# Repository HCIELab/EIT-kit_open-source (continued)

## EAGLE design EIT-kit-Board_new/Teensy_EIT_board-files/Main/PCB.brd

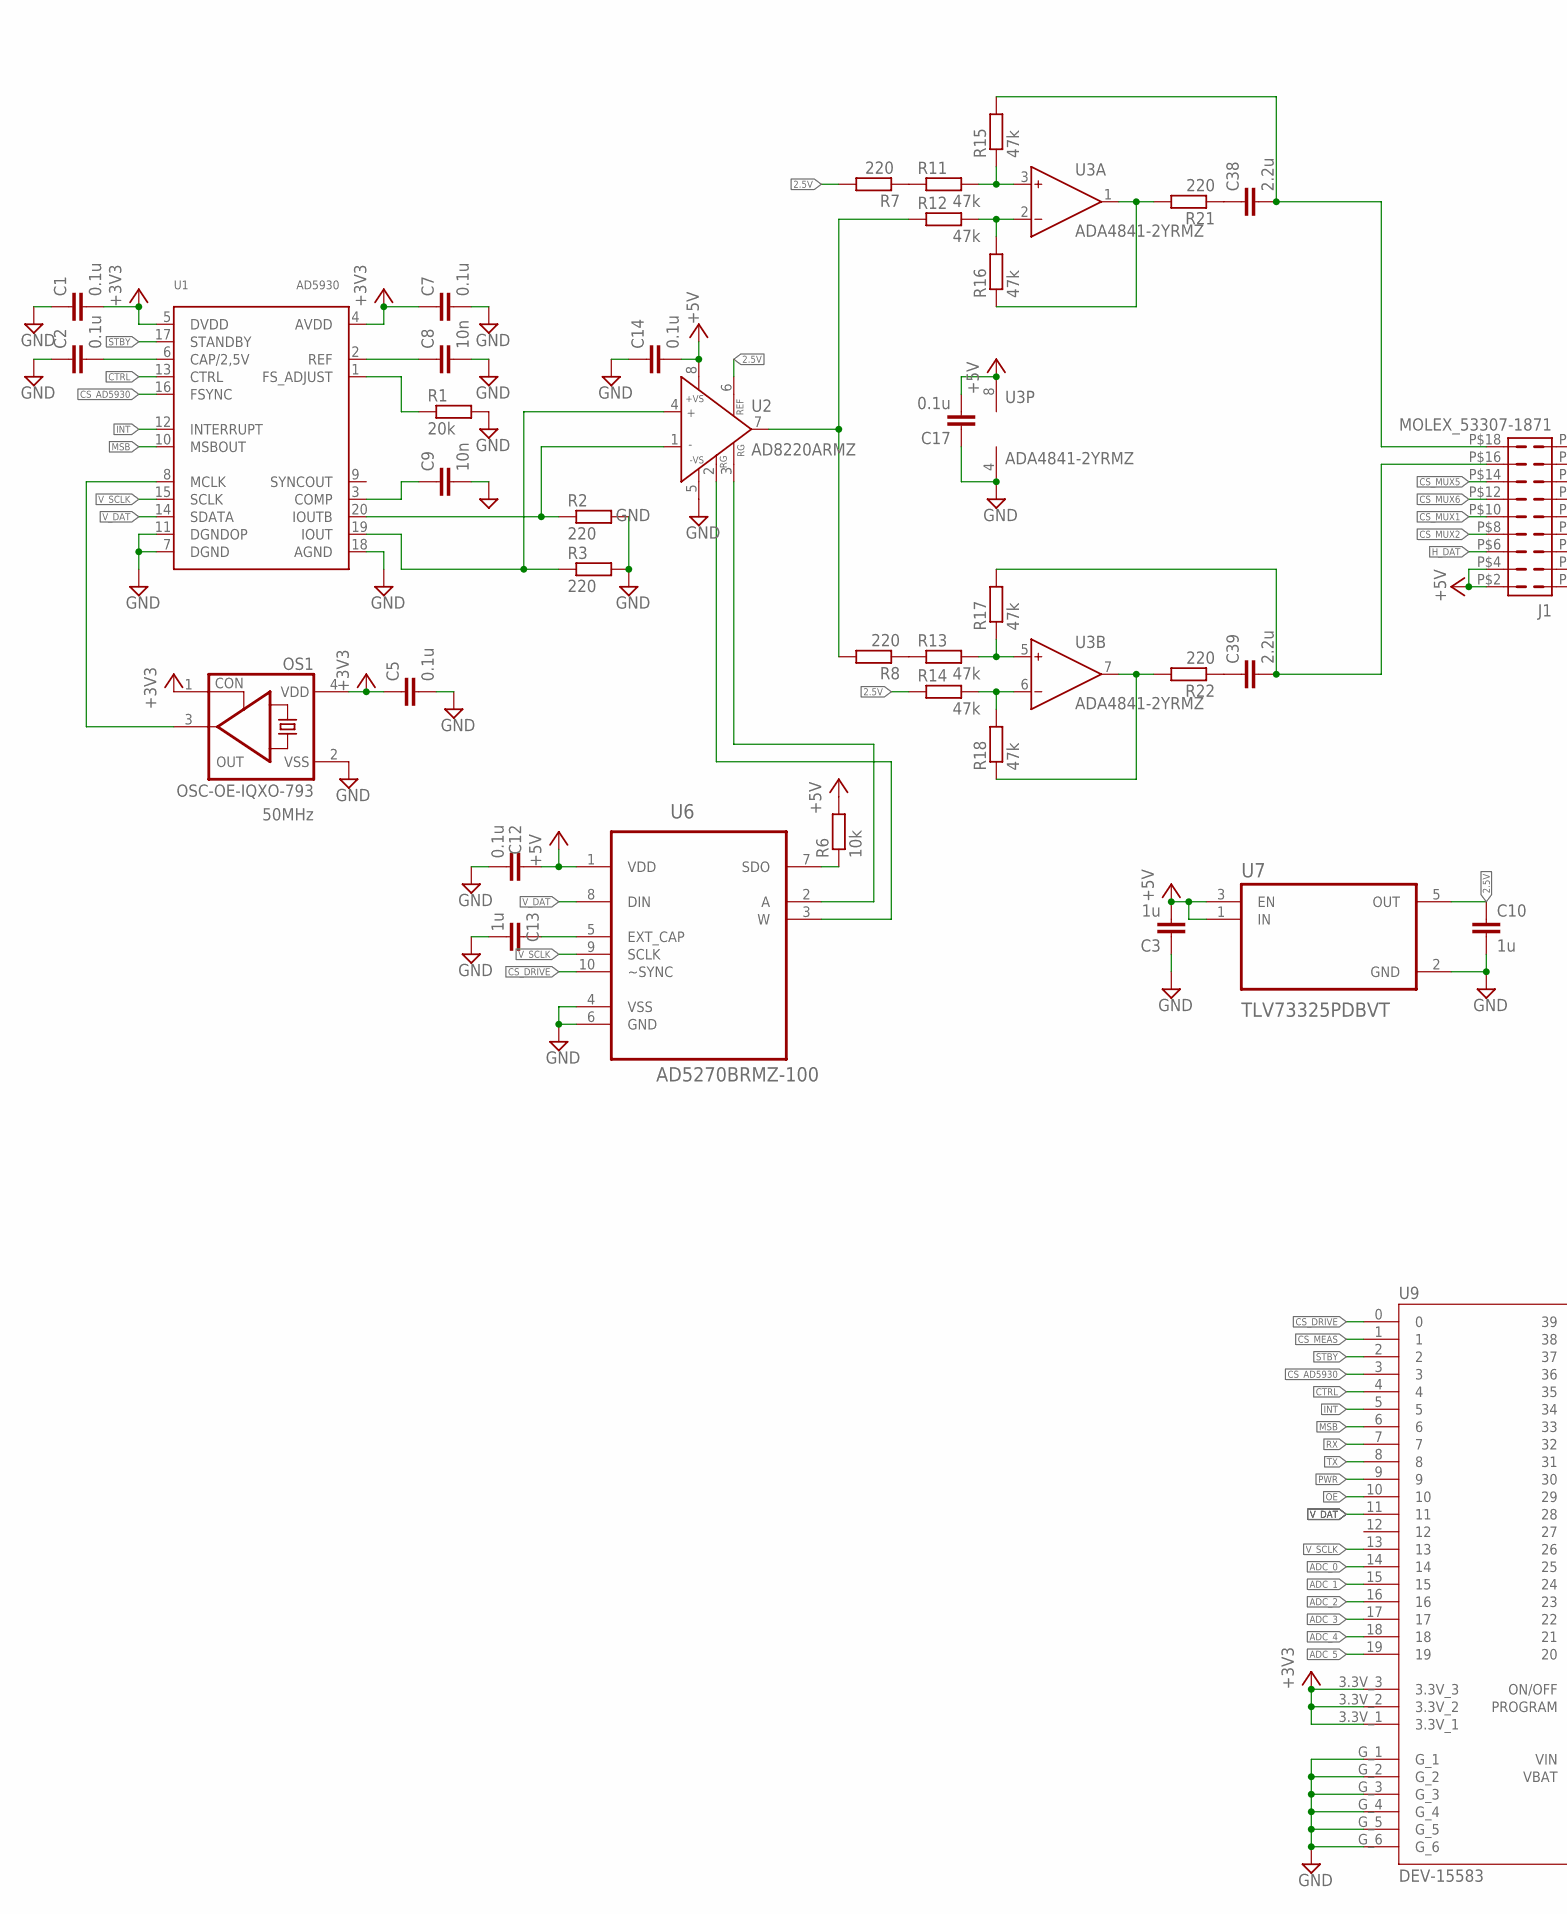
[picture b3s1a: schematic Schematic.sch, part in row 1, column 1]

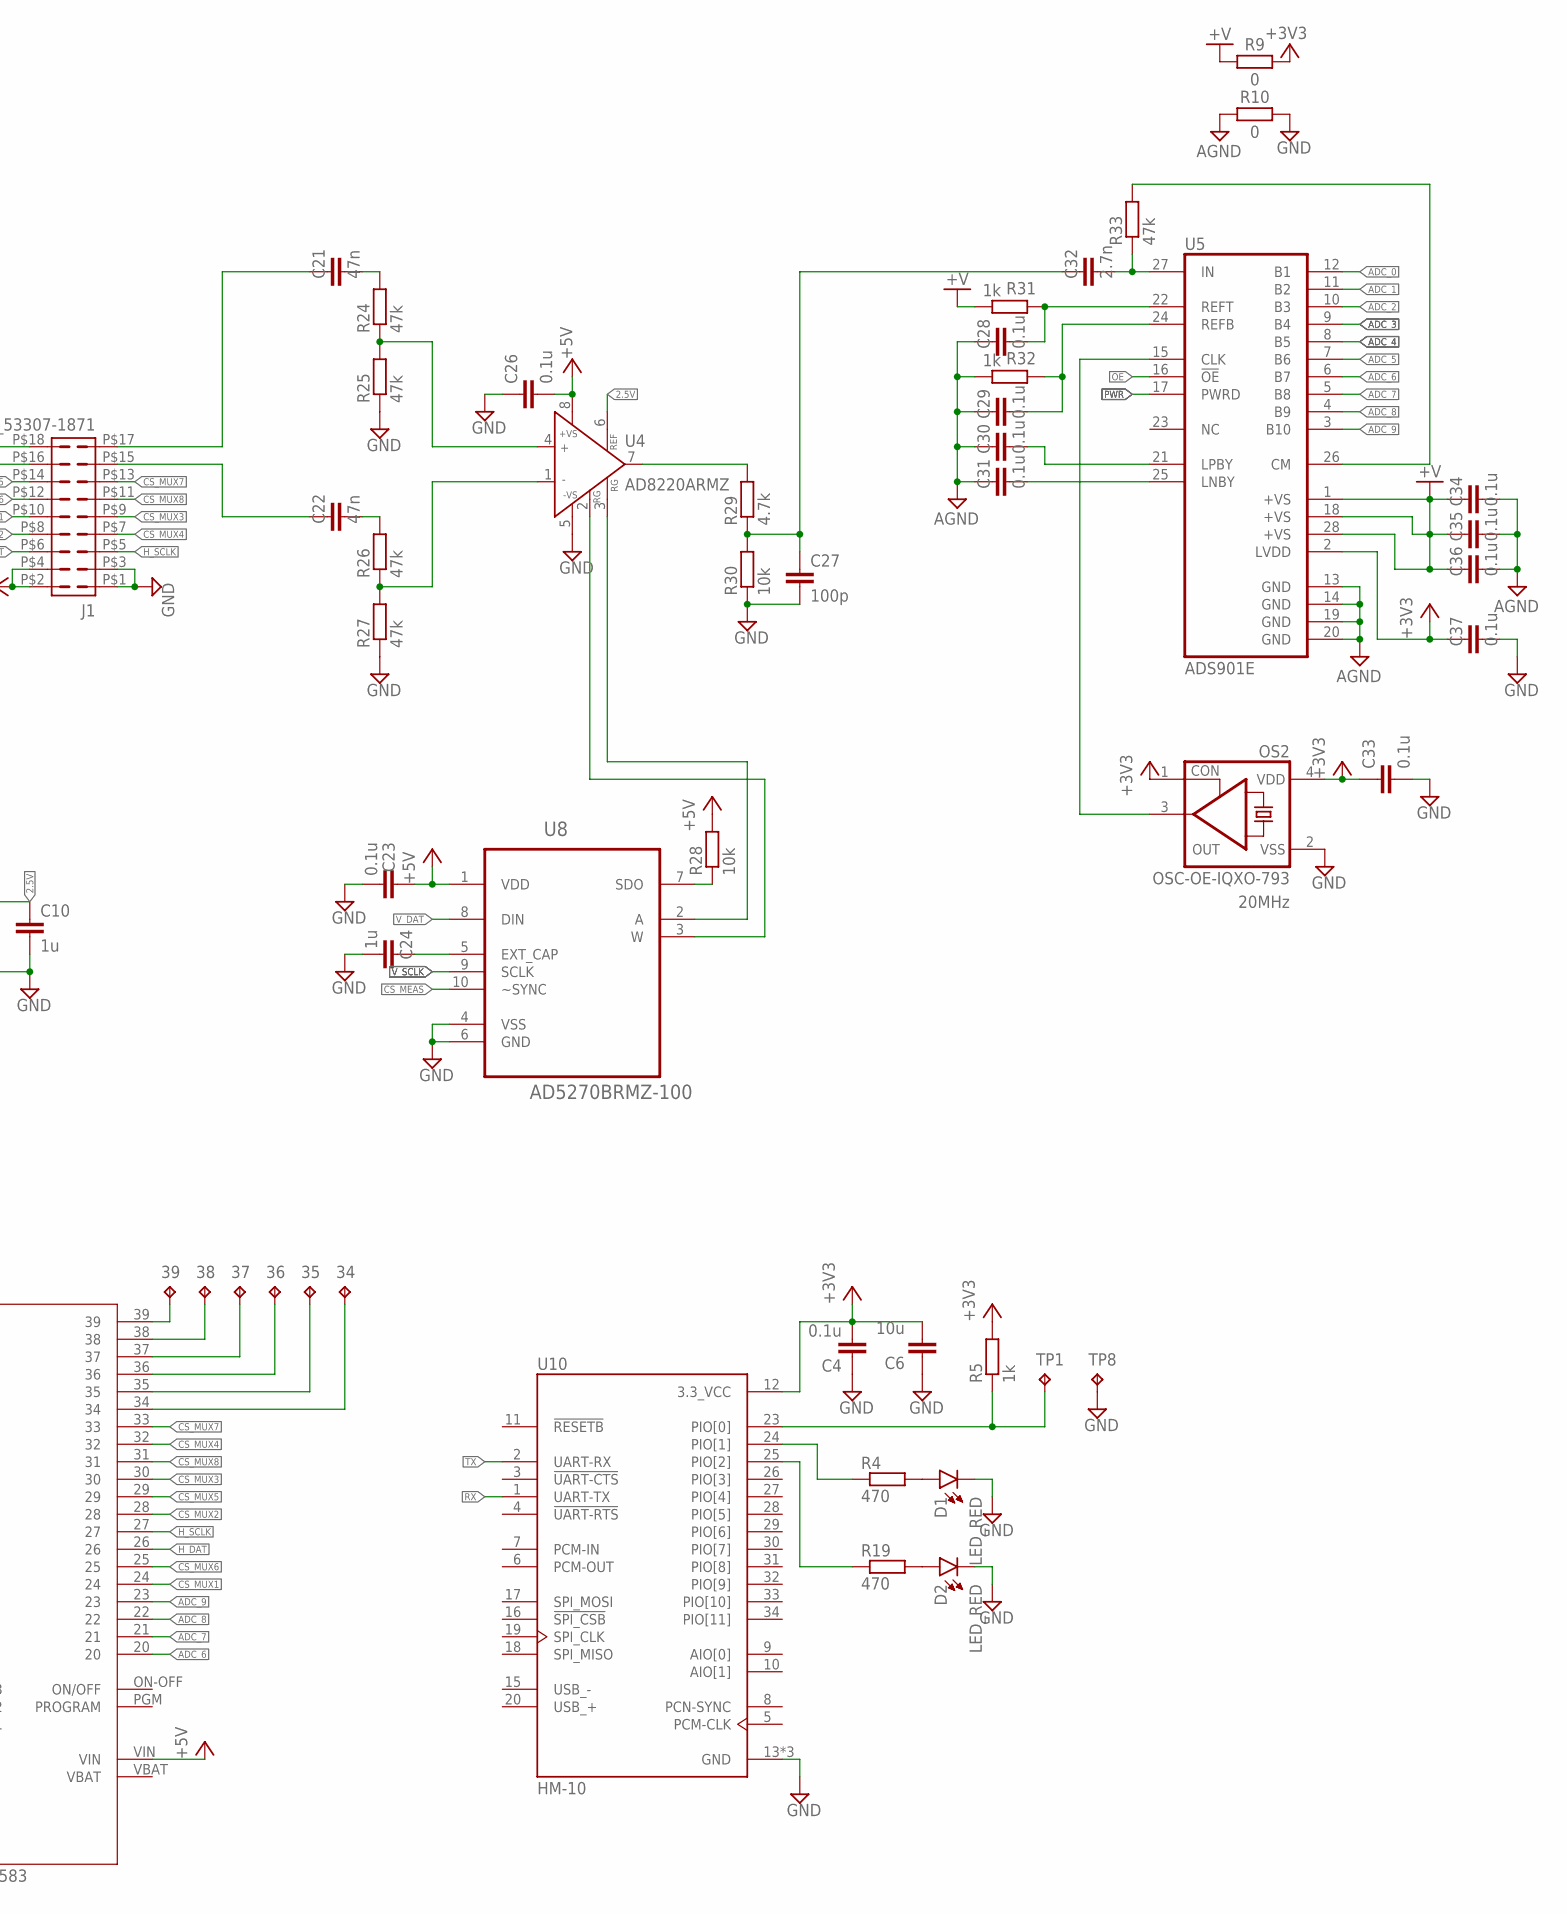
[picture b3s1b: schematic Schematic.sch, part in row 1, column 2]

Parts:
34, 35, 36, 37, 38, 39: TPTP13R; TP13R
C1, C2, C4, C5, C7, C12, C14, C17, C23, C26: 0.1u; C0603
C3, C10, C13, C24: 1u; C0603
C6: 10u; CAPC2012X110
C8, C9: 10n; C0603
C21, C22: 47n; C0603
C27: 100p; C0603
C28, C29, C30, C31, C33, C34, C35, C36, C37: 0.1u; CAPC1005X60
C32: 2.7n; CAPC1005X60
C38, C39: 2.2u; C0603
D1, D2: LED_RED; LEDC1608X65N_RND-R
J1: MOLEX_53307-1871
OS1, OS2: OSC-OE-IQXO-793; 2.5X2-4-PAD
R1: 20k; R0603
R2, R3, R7, R8, R21, R22: 220; R0603
R4, R19: 470; R0603
R5: 1k; R0603
R6, R28, R30: 10k; R0603
R9, R10: 0; RESC1608X60
R11, R12, R13, R14, R15, R16, R17, R18, R24, R25, R26, R27: 47k; R0603
R29: 4.7k; R0603
R31, R32: 1k; RESC1005X40
R33: 47k; RESC1005X40
TP1, TP8: TPTP20SQ; TP20SQ
U1: AD5930; TSSOP20
U2, U4: AD8220ARMZ; MSOP8
U3: ADA4841-2YRMZ; MSOP8
U5: ADS901E; SSOP28BU
U6, U8: AD5270BRMZ-100; SOP50P490X110-10N
U7: TLV73325PDBVT; SOT95P280X145-5N
U9: DEV-15583; MODULE_DEV-15583
U10: HM-10

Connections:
2.5V: C10.1, R7.2, R14.1, U2.6 (REF), U4.6 (REF), U7.5 (OUT)
+3V3: C1.2, C4.2, C5.1, C6.2, C7.1, C33.1, C37.1, OS1.1 (CON), OS1.4 (VDD), OS2.1 (CON), OS2.4 (VDD), R5.2, R9.2, U1.4 (AVDD), U1.5 (DVDD), U5.2 (LVDD), U9.3.3V_1, U9.3.3V_2, U9.3.3V_3, U10.12 (3.3_VCC)
+5V: C3.2, C12.1, C14.2, C17.2, C23.1, C26.2, J1.P$2 (2), J1.P$4 (4), R6.2, R28.2, U2.8 (+VS), U3.8 (V+), U4.8 (+VS), U6.1 (VDD), U7.1 (IN), U7.3 (EN), U8.1 (VDD), U9.VIN
+V: C34.1, C35.1, C36.1, R9.1, R31.2, U5.1 (+VS), U5.18 (+VS), U5.28 (+VS)
ADC_0: U5.12 (B1), U9.14
ADC_1: U5.11 (B2), U9.15
ADC_2: U5.10 (B3), U9.16
ADC_3: U5.9 (B4), U9.17
ADC_4: U5.8 (B5), U9.18
ADC_5: U5.7 (B6), U9.19
ADC_6: U5.6 (B7), U9.20
ADC_7: U5.5 (B8), U9.21
ADC_8: U5.4 (B9), U9.22
ADC_9: U5.3 (B10), U9.23
AGND: C28.1, C29.1, C30.1, C31.1, C34.2, C35.2, C36.2, R10.1, R32.2, U5.13 (GND), U5.14 (GND), U5.19 (GND), U5.20 (GND)
CS_AD5930: U1.16 (FSYNC), U9.3
CS_DRIVE: U6.10 (~SYNC), U9.0
CS_MEAS: U8.10 (~SYNC), U9.1
CS_MUX1: J1.P$10 (10), U9.24
CS_MUX2: J1.P$8 (8), U9.28
CS_MUX3: J1.P$9 (9), U9.30
CS_MUX4: J1.P$7 (7), U9.32
CS_MUX5: J1.P$14 (14), U9.29
CS_MUX6: J1.P$12 (12), U9.25
CS_MUX7: J1.P$13 (13), U9.33
CS_MUX8: J1.P$11 (11), U9.31
CTRL: U1.13 (CTRL), U9.4
GND: C1.1, C2.1, C3.1, C4.1, C5.2, C6.1, C7.2, C8.2, C9.2, C10.2, C12.2, C13.2, C14.1, C17.1, C23.2, C24.2, C26.1, C27.2, C33.2, C37.2, D1.C, D2.C, J1.P$1 (1), J1.P$3 (3), OS1.2 (VSS), OS2.2 (VSS), R1.2, R2.2, R3.2, R10.2, R25.1, R27.1, R30.1, TP8.TP, U1.7 (DGND), U1.11 (DGNDOP), U1.18 (AGND), U2.5 (-VS), U3.4 (V-), U4.5 (-VS), U6.4 (VSS), U6.6 (GND), U7.2 (GND), U8.4 (VSS), U8.6 (GND), U9.G_1, U9.G_2, U9.G_3, U9.G_4, U9.G_5, U9.G_6, U10.13 (GND), U10.21 (GND), U10.22 (GND)
H_DAT: J1.P$6 (6), U9.26
H_SCLK: J1.P$5 (5), U9.27
INT: U1.12 (INTERRUPT), U9.5
MSB: U1.10 (MSBOUT), U9.6
unnamed: R1.1, U1.1 (FS_ADJUST)
unnamed: C8.1, U1.2 (REF)
unnamed: C9.1, U1.3 (COMP)
unnamed: R2.1, U1.20 (IOUTB), U2.1 (IN-)
unnamed: R3.1, U1.19 (IOUT), U2.4 (IN+)
unnamed: R7.1, R11.1
unnamed: R8.1, R13.1
unnamed: R14.2, R18.2, U3.6 (IN-)
unnamed: R13.2, R17.1, U3.5 (IN+)
unnamed: R11.2, R15.1, U3.3 (IN+)
unnamed: R12.2, R16.2, U3.2 (IN-)
unnamed: R16.1, R21.2, U3.1 (OUT)
unnamed: OS1.3 (OUT), U1.8 (MCLK)
unnamed: C2.2, U1.6 (CAP/2,5V)
unnamed: R18.1, R22.2, U3.7 (OUT)
unnamed: R6.1, U6.7 (SDO)
unnamed: C22.1, J1.P$15 (15)
unnamed: C21.1, J1.P$17 (17)
unnamed: U2.2 (RG), U6.3 (W)
unnamed: R8.2, R12.1, U2.7 (OUT)
unnamed: U2.3 (RG), U6.2 (A)
unnamed: C13.1, U6.5 (EXT_CAP)
unnamed: R28.1, U8.7 (SDO)
unnamed: R33.2, U5.26 (CM)
unnamed: C32.2, R33.1, U5.27 (IN)
unnamed: C24.1, U8.5 (EXT_CAP)
unnamed: C28.2, R31.1, U5.22 (REFT)
unnamed: C29.2, R32.1, U5.24 (REFB)
unnamed: C31.2, U5.25 (LNBY)
unnamed: C30.2, U5.21 (LPBY)
unnamed: U4.2 (RG), U8.3 (W)
unnamed: OS2.3 (OUT), U5.15 (CLK)
unnamed: R29.2, U4.7 (OUT)
unnamed: C21.2, R24.2
unnamed: R24.1, R25.2, U4.4 (IN+)
unnamed: R26.1, R27.2, U4.1 (IN-)
unnamed: C22.2, R26.2
unnamed: C38.2, J1.P$18 (18), R15.2
unnamed: U4.3 (RG), U8.2 (A)
unnamed: C27.1, C32.1, R29.1, R30.2
unnamed: D1.A, R4.2
unnamed: R5.1, TP1.TP, U10.23 (PIO[0])
unnamed: R4.1, U10.24 (PIO[1])
unnamed: D2.A, R19.2
unnamed: R19.1, U10.25 (PIO[2])
unnamed: 39.TP, U9.39
unnamed: 38.TP, U9.38
unnamed: 37.TP, U9.37
unnamed: 36.TP, U9.36
unnamed: 35.TP, U9.35
unnamed: 34.TP, U9.34
unnamed: C39.2, J1.P$16 (16), R17.2
unnamed: C38.1, R21.1
unnamed: C39.1, R22.1
OE: U5.16 (!OE), U9.10
PWR: U5.17 (PWRD), U9.9
RX: U9.7, U10.1 (UART-TX)
STBY: U1.17 (STANDBY), U9.2
TX: U9.8, U10.2 (UART-RX)
VBAT: U9.VBAT
V_DAT: U1.14 (SDATA), U6.8 (DIN), U8.8 (DIN), U9.11
V_SCLK: U1.15 (SCLK), U6.9 (SCLK), U8.9 (SCLK), U9.13

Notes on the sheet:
50MHz
20MHz

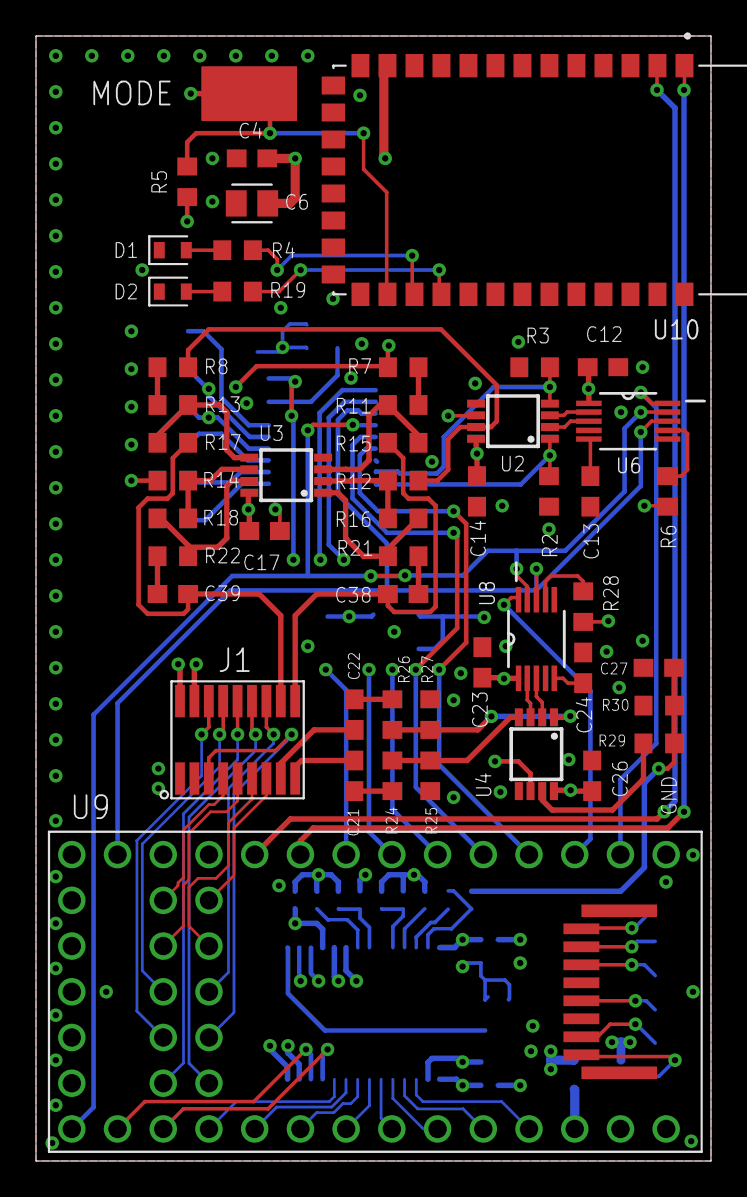
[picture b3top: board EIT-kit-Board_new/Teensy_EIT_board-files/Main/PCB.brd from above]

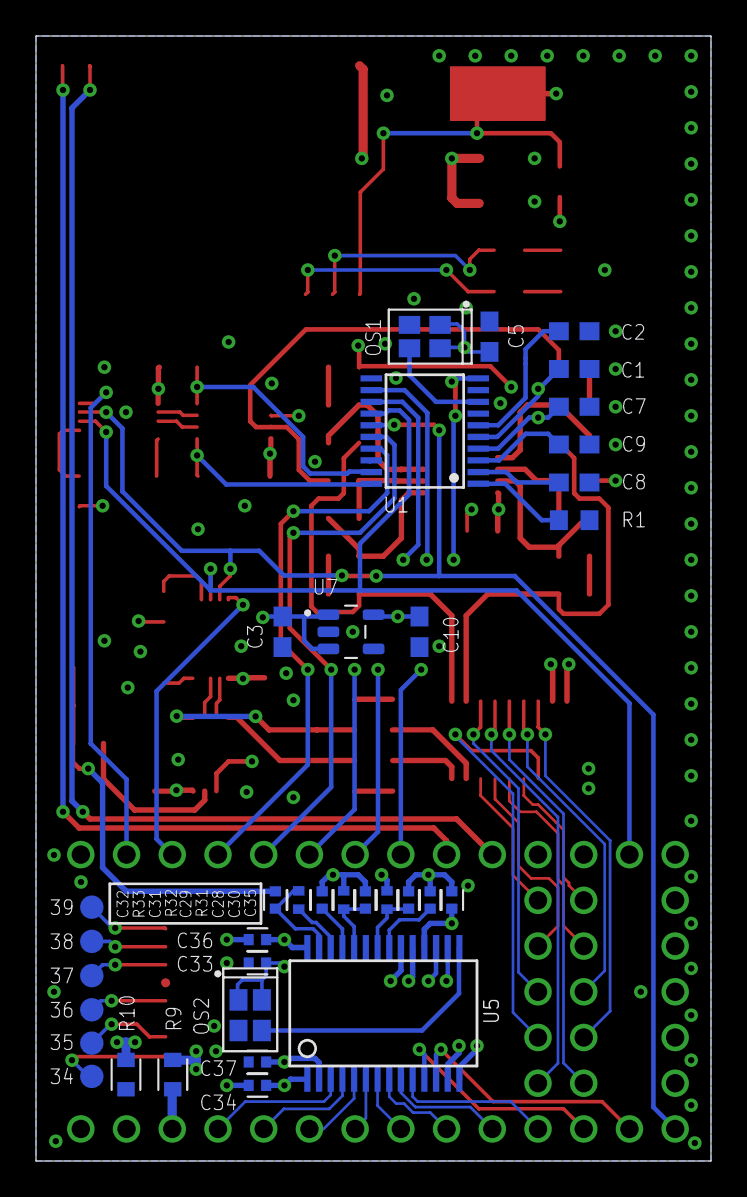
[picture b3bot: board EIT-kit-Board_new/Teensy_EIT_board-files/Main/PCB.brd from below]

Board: 4 copper layers, 37.5 x 62.5 mm, 86 parts (35 on the bottom side), 93 nets.

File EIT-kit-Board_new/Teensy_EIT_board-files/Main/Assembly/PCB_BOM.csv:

Qty,Value,Device,Package,Parts,Description
2,0,R_CHIP-0603(1608-METRIC),RESC1608X60,"R9, R10",Resistor Fixed - Generic
10,0.1u,C-EUC0603,C0603,"C1, C2, C4, C5, C7, C12, C14, C17, C23, C26","CAPACITOR, European symbol"
9,0.1u,C_CHIP-0402(1005-METRIC),CAPC1005X60,"C28, C29, C30, C31, C33, C34, C35, C36, C37",Capacitor - Generic
1,100p,C-EUC0603,C0603,C27,"CAPACITOR, European symbol"
3,10k,R-EU_R0603,R0603,"R6, R28, R30","RESISTOR, European symbol"
2,10n,C-EUC0603,C0603,"C8, C9","CAPACITOR, European symbol"
1,10u,C_CHIP-0805(2012-METRIC),CAPC2012X110,C6,Capacitor - Generic
1,1k,R-EU_R0603,R0603,R5,"RESISTOR, European symbol"
2,1k,R_CHIP-0402(1005-METRIC),RESC1005X40,"R31, R32",Resistor Fixed - Generic
4,1u,C-EUC0603,C0603,"C3, C10, C13, C24","CAPACITOR, European symbol"
2,2.2u,C-EUC0603,C0603,"C38, C39","CAPACITOR, European symbol"
1,2.7n,C_CHIP-0402(1005-METRIC),CAPC1005X60,C32,Capacitor - Generic
1,20k,R-EU_R0603,R0603,R1,"RESISTOR, European symbol"
6,220,R-EU_R0603,R0603,"R2, R3, R7, R8, R21, R22","RESISTOR, European symbol"
1,4.7k,R-EU_R0603,R0603,R29,"RESISTOR, European symbol"
2,470,R-EU_R0603,R0603,"R4, R19","RESISTOR, European symbol"
12,47k,R-EU_R0603,R0603,"R11, R12, R13, R14, R15, R16, R17, R18, R24, R25, R26, R27","RESISTOR, European symbol"
1,47k,R_CHIP-0402(1005-METRIC),RESC1005X40,R33,Resistor Fixed - Generic
2,47n,C-EUC0603,C0603,"C21, C22","CAPACITOR, European symbol"
2,AD5270BRMZ-100,AD5270BRMZ-100,SOP50P490X110-10N,"U6, U8","1024-/256-Position, 1% Resistor Tolerance Error, SPI Interface and 50-TP Memory Digital Rheostat  Check prices"
1,AD5930,AD5930,TSSOP20,U1,Programmable Waveform Generator
2,AD8220ARMZ,AD8220ARMZ,MSOP8,"U2, U4","Single-Supply, Rail-to-Rail, Low Power, FET Input Op Amp"
1,ADA4841-2YRMZ,ADA4841-2YRMZ,MSOP8,U3,Ultralow Noise Amplifier at Lower Power
1,ADS901E,ADS901E,SSOP28BU,U5,"10-Bit, 20 MSPS ADC SE/Diff Inputs"
1,DEV-15583,DEV-15583,MODULE_DEV-15583,U9,RT1062 Teensy 4.0 i.MX ARM® Cortex®-M7 MPU Embedded Evaluation Board Check prices
1,HM-10,HM-10,,U10,Bluetooth to Serial Port Module Check prices
2,LED_RED,CHIP-ROUND-R_0603,LEDC1608X65N_RND-R,"D1, D2",LED - Generic
1,MOLEX_53307-1871,MOLEX_53307-1871,MOLEX_53307-1871,J1,"2x9 connector, female"
1,ECS-2520MV-500-BL-TR,ECS-2520MV-500-BL-TR,2.5X2-4-PAD,OS1,50MHz OSCILLATOR WITH OE
1,SXO22C3C381-20.000M,SXO22C3C381-20.000M,2.5X2-4-PAD,OS2,20MHz OSCILLATOR WITH OE
1,TLV73325PDBVT,TLV73325PDBVT,SOT95P280X145-5N,U7,Check prices

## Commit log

2021-10-15 update EIT-kit board files and arduino library
2021-10-15 add EAGLE version of the EIT-kit board as well
2022-05-30 mux1 & mux2 files
2022-06-06 update bom files for mux1 & mux2
2022-09-01 upload new EIT sensing board design
2023-05-01 upload an example arduino file for EIT-kit Arduino library
